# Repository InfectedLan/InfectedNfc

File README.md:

# InfectedNfc
Repository containing coumentation on our upcoming NFC platform

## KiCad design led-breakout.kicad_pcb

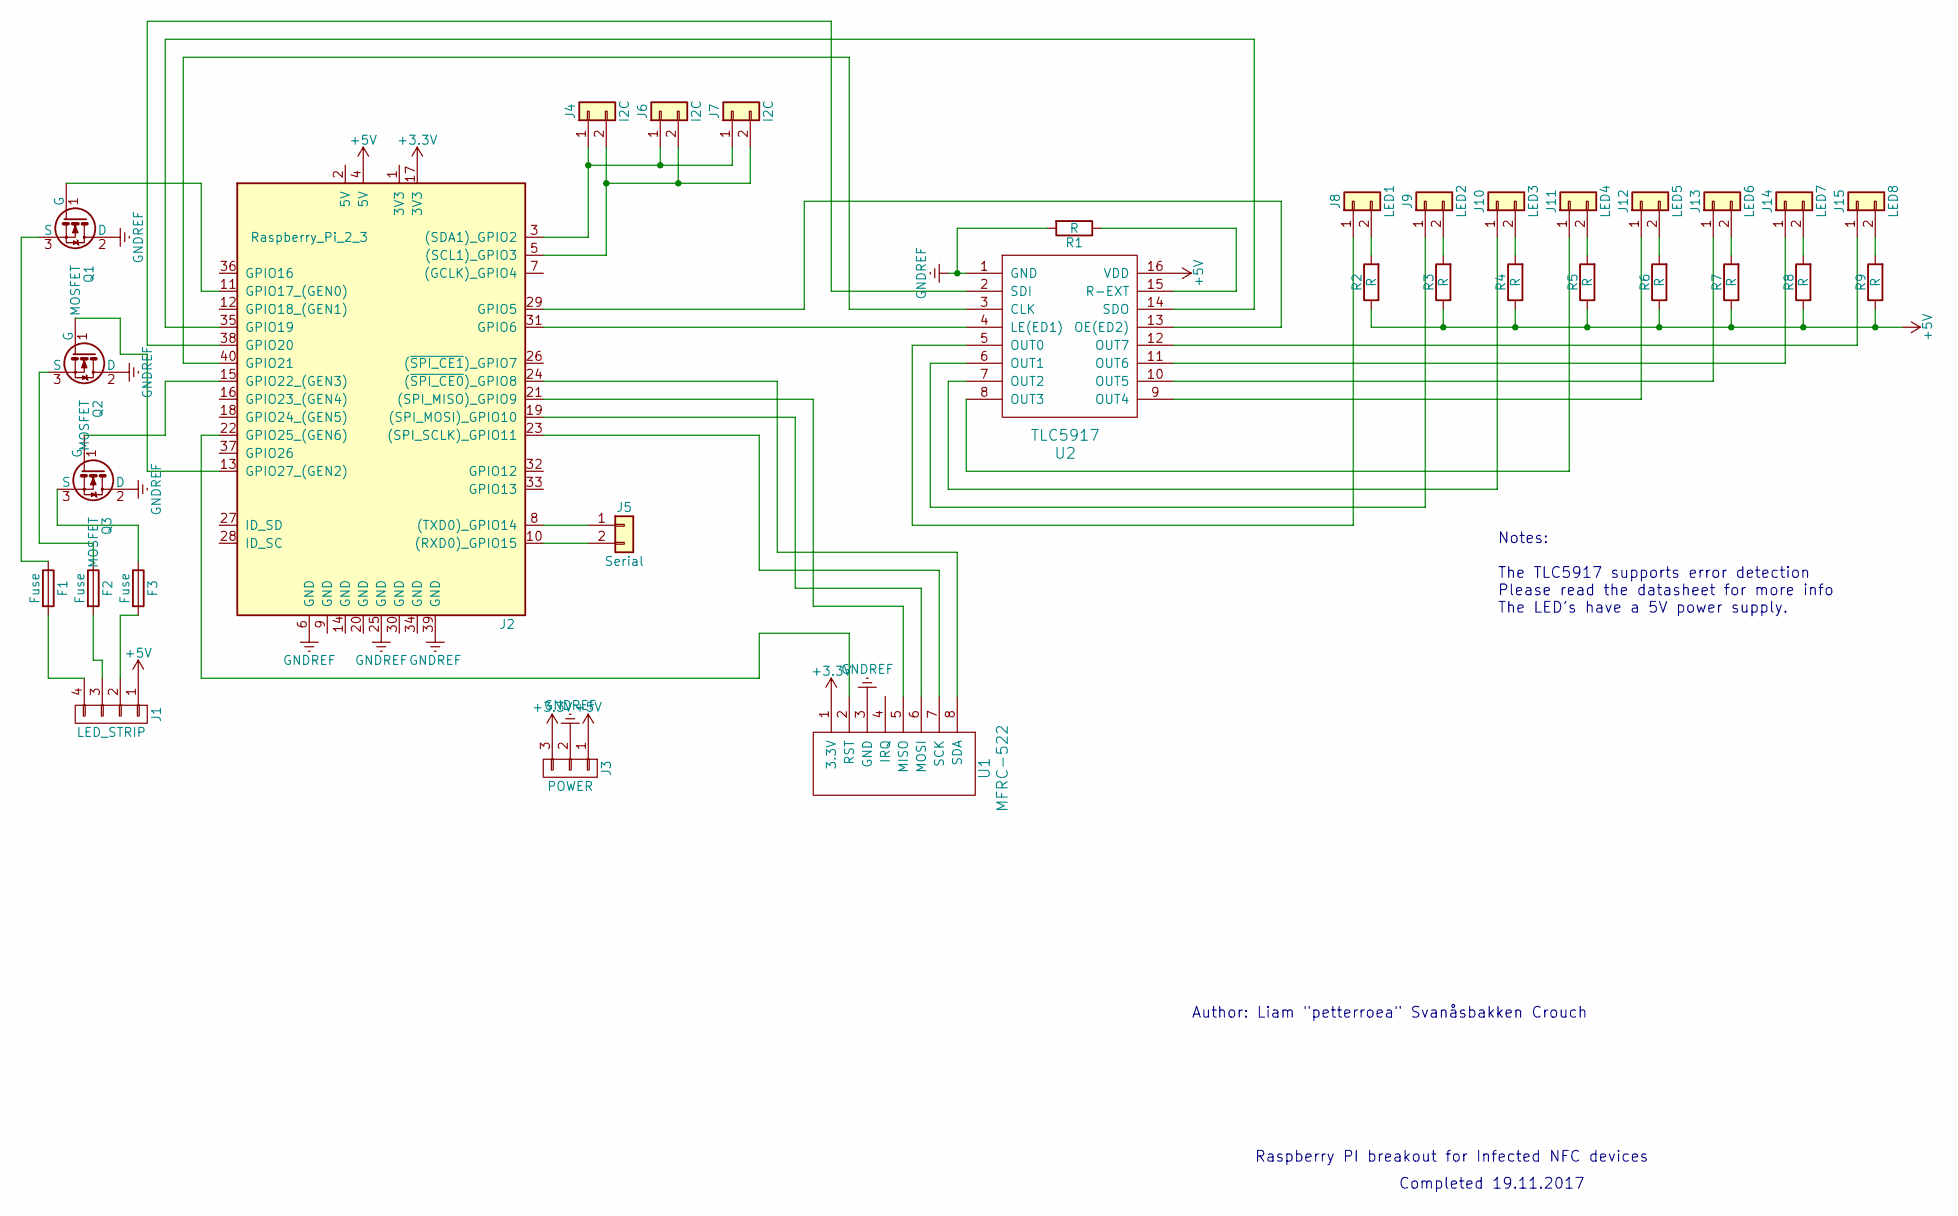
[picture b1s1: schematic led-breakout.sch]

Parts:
F1, F2, F3: Fuse; Fuse_SMD1206_HandSoldering
J1: LED_STRIP; Socket_Strip_Straight_1x04_Pitch2.54mm
J2: Raspberry_Pi_2_3; Pin_Header_Straight_2x20_Pitch2.54mm
J3: POWER; Socket_Strip_Straight_1x03_Pitch2.54mm
J4, J6, J7: I2C; Socket_Strip_Straight_1x02_Pitch2.54mm
J5: Serial; Socket_Strip_Straight_1x02_Pitch2.54mm
J8: LED1; Socket_Strip_Straight_1x02_Pitch2.54mm
J9: LED2; Socket_Strip_Straight_1x02_Pitch2.54mm
J10: LED3; Socket_Strip_Straight_1x02_Pitch2.54mm
J11: LED4; Socket_Strip_Straight_1x02_Pitch2.54mm
J12: LED5; Socket_Strip_Straight_1x02_Pitch2.54mm
J13: LED6; Socket_Strip_Straight_1x02_Pitch2.54mm
J14: LED7; Socket_Strip_Straight_1x02_Pitch2.54mm
J15: LED8; Socket_Strip_Straight_1x02_Pitch2.54mm
Q1, Q2, Q3: MOSFET; SOT-223-3_TabPin2
R1, R2, R3, R4, R5, R6, R7, R8, R9: R; R_Axial_DIN0207_L6.3mm_D2.5mm_P10.16mm_Horizontal
U1: MFRC-522; Socket_Strip_Straight_1x08_Pitch2.54mm
U2: TLC5917; DIP-16_W10.16mm

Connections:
+3V3: J2.17 (3V3), J3.3, U1.1 (3.3V)
+5V: J1.1, J2.4 (5V), J3.1, R2.1, R3.1, R4.1, R5.1, R6.1, R7.1, R8.1, R9.1, U2.16 (VDD)
GNDREF: J2.6 (GND), J2.25 (GND), J2.39 (GND), J3.2, Q1.2 (D), Q2.2 (D), Q3.2 (D), R1.2, U1.3 (GND), U2.1 (GND)
unnamed: F1.1, Q1.3 (S)
unnamed: F1.2, J1.4
unnamed: F2.1, Q2.3 (S)
unnamed: F2.2, J1.3
unnamed: F3.1, Q3.3 (S)
unnamed: F3.2, J1.2
unnamed: J2.3 ((SDA1)_GPIO2), J4.1, J6.1, J7.1
unnamed: J2.5 ((SCL1)_GPIO3), J4.2, J6.2, J7.2
unnamed: J2.8 ((TXD0)_GPIO14), J5.1
unnamed: J2.10 ((RXD0)_GPIO15), J5.2
unnamed: J2.11 (GPIO17_(GEN0)), Q1.1 (G)
unnamed: J2.13 (GPIO27_(GEN2)), Q2.1 (G)
unnamed: J2.15 (GPIO22_(GEN3)), Q3.1 (G)
unnamed: J2.19 ((SPI_MOSI)_GPIO10), U1.6 (MOSI)
unnamed: J2.21 ((SPI_MISO)_GPIO9), U1.5 (MISO)
unnamed: J2.22 (GPIO25_(GEN6)), U1.2 (RST)
unnamed: J2.23 ((SPI_SCLK)_GPIO11), U1.7 (SCK)
unnamed: J2.24 ((~SPI_CE0~)_GPIO8), U1.8 (SDA)
unnamed: J2.29 (GPIO5), U2.13 (OE(ED2))
unnamed: J2.31 (GPIO6), U2.4 (LE(ED1))
unnamed: J2.35 (GPIO19), U2.14 (SDO)
unnamed: J2.38 (GPIO20), U2.2 (SDI)
unnamed: J2.40 (GPIO21), U2.3 (CLK)
unnamed: J8.1, U2.5 (OUT0)
unnamed: J8.2, R2.2
unnamed: J9.1, U2.6 (OUT1)
unnamed: J9.2, R3.2
unnamed: J10.1, U2.7 (OUT2)
unnamed: J10.2, R4.2
unnamed: J11.1, U2.8 (OUT3)
unnamed: J11.2, R5.2
unnamed: J12.1, U2.9 (OUT4)
unnamed: J12.2, R6.2
unnamed: J13.1, U2.10 (OUT5)
unnamed: J13.2, R7.2
unnamed: J14.1, U2.11 (OUT6)
unnamed: J14.2, R8.2
unnamed: J15.1, U2.12 (OUT7)
unnamed: J15.2, R9.2
unnamed: R1.1, U2.15 (R-EXT)

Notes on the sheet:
Completed 19.11.2017
Raspberry PI breakout for Infected NFC devices
Author: Liam "petterroea" Svanåsbakken Crouch
Notes: The TLC5917 supports error detection Please read the datasheet for more info The LED's have a 5V power supply.

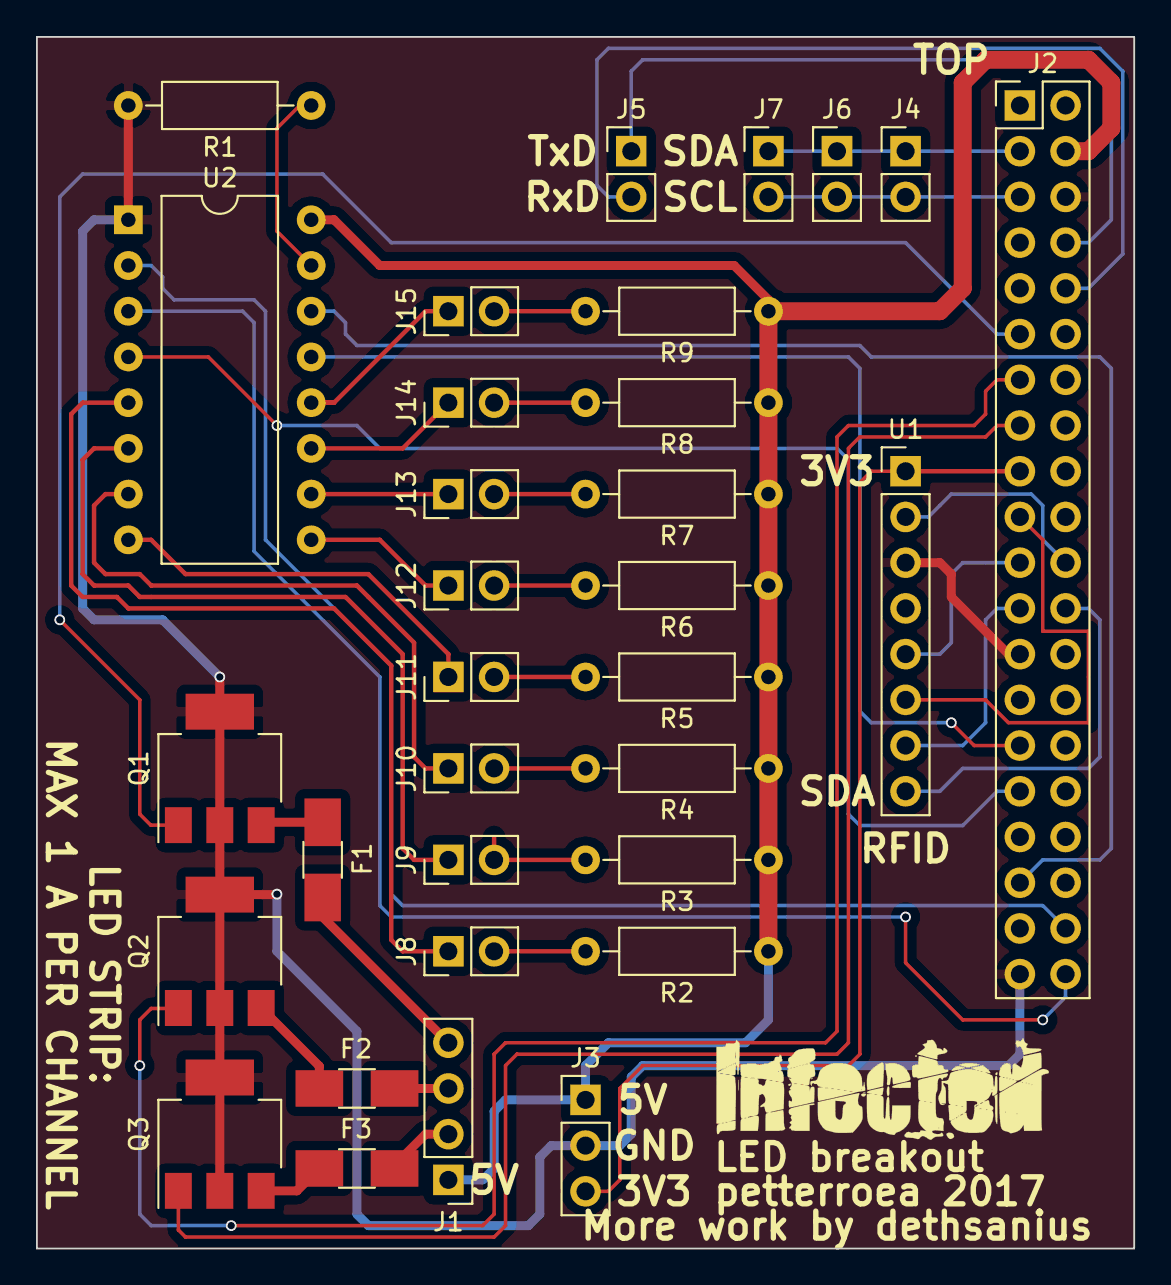
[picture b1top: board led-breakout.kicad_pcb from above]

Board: 2 copper layers, 61.0 x 67.3 mm, 32 parts (0 on the bottom side), 43 nets.

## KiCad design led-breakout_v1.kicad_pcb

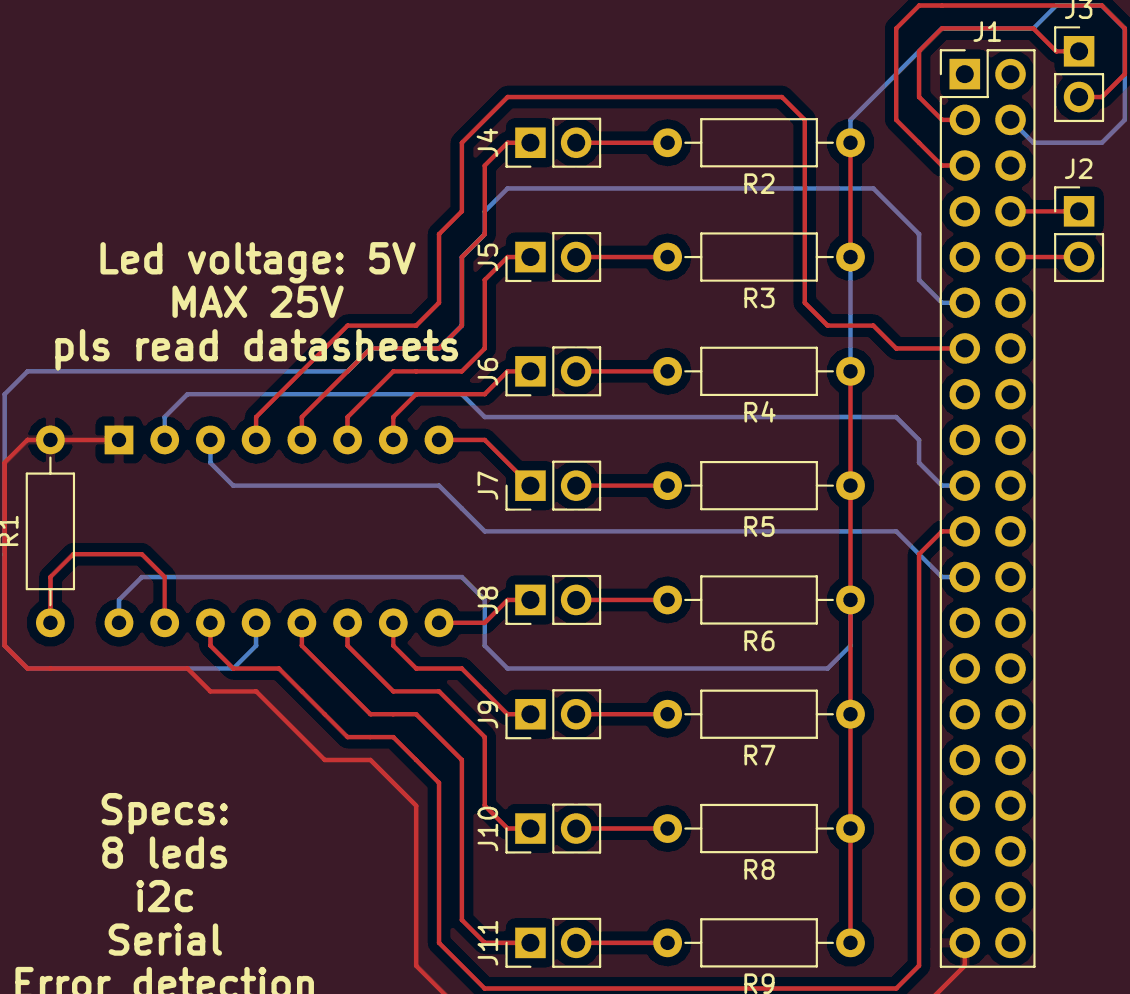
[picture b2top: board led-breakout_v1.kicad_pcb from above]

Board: 2 copper layers, 21 parts (1 on the bottom side), 28 nets.

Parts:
J1: Raspberry_Pi_2_3; Pin_Header_Straight_2x20_Pitch2.54mm
J2: Serial; Socket_Strip_Straight_1x02_Pitch2.54mm
J3: I2C; Socket_Strip_Straight_1x02_Pitch2.54mm
J4: LED1; Socket_Strip_Straight_1x02_Pitch2.54mm
J5: LED2; Socket_Strip_Straight_1x02_Pitch2.54mm
J6: LED3; Socket_Strip_Straight_1x02_Pitch2.54mm
J7: LED4; Socket_Strip_Straight_1x02_Pitch2.54mm
J8: LED5; Socket_Strip_Straight_1x02_Pitch2.54mm
J9: LED6; Socket_Strip_Straight_1x02_Pitch2.54mm
J10: LED7; Socket_Strip_Straight_1x02_Pitch2.54mm
J11: LED8; Socket_Strip_Straight_1x02_Pitch2.54mm
R1, R2, R3, R4, R5, R6, R7, R8, R9: R; R_Axial_DIN0207_L6.3mm_D2.5mm_P10.16mm_Horizontal
U1: TLC5917; DIP-16_W10.16mm

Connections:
+5V: J1.4, R2.1, R3.1, R4.1, R5.1, R6.1, R7.1, R8.1, R9.1, U1.16
GNDREF: J1.39, R1.2, U1.1
unnamed: J1.3, J3.1
unnamed: J1.5, J3.2
unnamed: J1.8, J2.1
unnamed: J1.10, J2.2
unnamed: J1.11, U1.13
unnamed: J1.13, U1.4
unnamed: J1.19, U1.2
unnamed: J1.21, U1.14
unnamed: J1.23, U1.3
unnamed: J4.1, U1.5
unnamed: J4.2, R2.2
unnamed: J5.1, U1.6
unnamed: J5.2, R3.2
unnamed: J6.1, U1.7
unnamed: J6.2, R4.2
unnamed: J7.1, U1.8
unnamed: J7.2, R5.2
unnamed: J8.1, U1.9
unnamed: J8.2, R6.2
unnamed: J9.1, U1.10
unnamed: J9.2, R7.2
unnamed: J10.1, U1.11
unnamed: J10.2, R8.2
unnamed: J11.1, U1.12
unnamed: J11.2, R9.2
unnamed: R1.1, U1.15

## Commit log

2017-11-21 initial board commit
2017-11-22 new revision
2017-11-23 hopefully last revision
2017-11-26 new revision of v3: now with filling
2017-12-06 Documentation
2017-12-06 led breakout v4
2017-12-09 Edge router path
2017-12-09 Parts list
